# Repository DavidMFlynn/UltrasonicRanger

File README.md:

# UltrasonicRanger
 Puts Ultrasonic range sensors on the serial bus

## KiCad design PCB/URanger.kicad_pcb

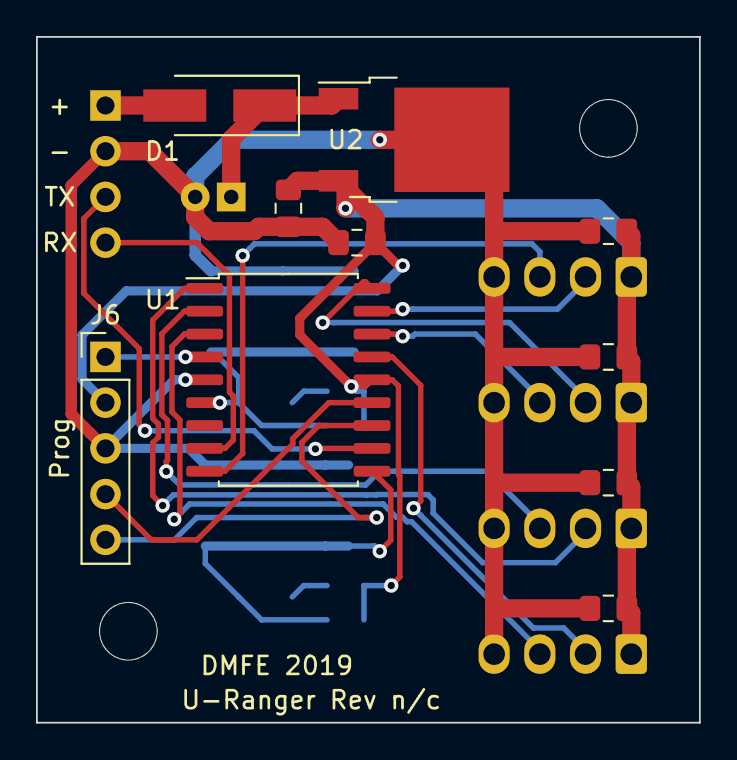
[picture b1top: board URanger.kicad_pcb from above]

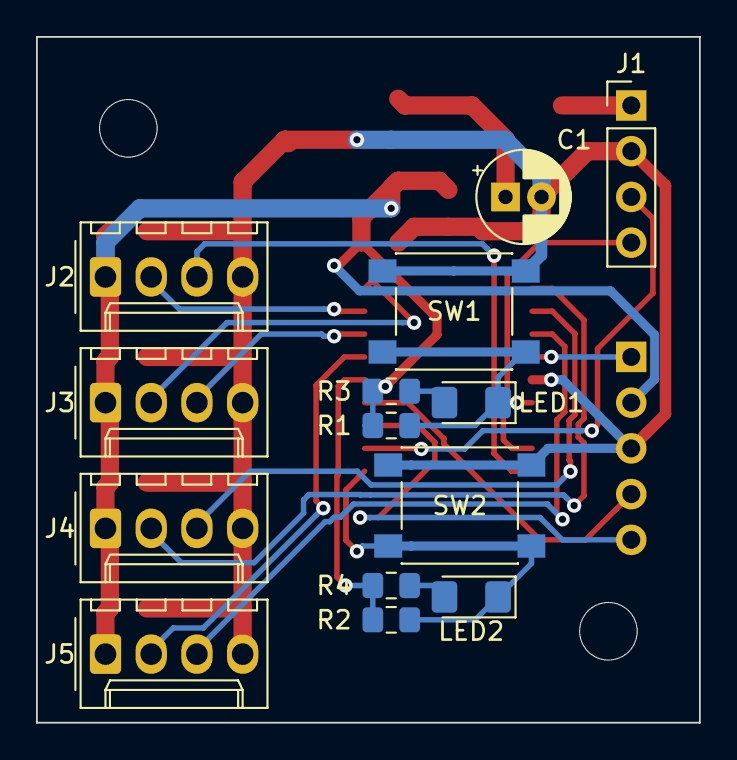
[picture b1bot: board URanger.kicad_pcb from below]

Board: 2 copper layers, 36.8 x 38.1 mm, 26 parts (14 on the bottom side), 21 nets.

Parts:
C1: 2.2uf; CP_Radial_D5.0mm_P2.00mm
C2, C3, C4, C5, C6, C7: 0.1uf; C_0805_2012Metric_Pad1.15x1.40mm_HandSolder
D1: D_ALT; D_SMA_Handsoldering
H1, H2: MountingHole_3.2mm_M3
J1: Conn_01x04; PinHeader_1x04_P2.54mm_Vertical
J2, J3, J4, J5: Conn_01x04; Molex_KK-254_AE-6410-04A_1x04_P2.54mm_Vertical
J6: Conn_01x05; PinHeader_1x05_P2.54mm_Vertical
LED1, LED2: LED_ALT; LED_1206_3216Metric_Pad1.42x1.75mm_HandSolder
R1, R2: 47K; R_0805_2012Metric_Pad1.15x1.40mm_HandSolder
R3, R4: 1.0K; R_0805_2012Metric_Pad1.15x1.40mm_HandSolder
SW1, SW2: SW_Push; SW_SPST_PTS645
U1: PIC16F648A-ISO; SOIC-18W_7.5x11.6mm_P1.27mm
U2: L7805; TO-252-2

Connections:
+5V: C2.1, C3.2, C4.1, C5.1, C6.1, C7.1, J2.1, J3.1, J4.1, J5.1, J6.2, R1.1, R2.1, R3.1, R4.1, U1.14, U2.3
+12V: D1.2, J1.1
Echo1: J2.3, U1.9
Echo2: J3.3, U1.16
Echo3: J4.3, U1.2
Echo4: J5.3, U1.3
GND: C1.2, C2.2, C3.1, C4.2, C5.2, C6.2, C7.2, J1.2, J2.4, J3.4, J4.4, J5.4, J6.3, SW1.1, SW2.1, U1.5, U2.2
ICSPCLK: J6.5, U1.12
ICSPDAT: J6.4, U1.13
unnamed: C1.1, D1.1, U2.1
unnamed: LED1.1, R1.2, SW1.2, U1.6
unnamed: LED1.2, R3.2
unnamed: LED2.1, R2.2, SW2.2, U1.10
unnamed: LED2.2, R4.2
RX: J1.4, U1.8
TX: J1.3, U1.11
Trig1: J2.2, U1.17
Trig2: J3.2, U1.18
Trig3: J4.2, U1.1
Trig4: J5.2, U1.15
Vpp: J6.1, U1.4

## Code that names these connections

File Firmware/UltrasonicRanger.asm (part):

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;   Pin 1 (RA2/AN2) Sensor 3 Trigger Pulse Output
;   Pin 2 (RA3/AN3) CCP3 Sensor 3 Echo Pulse Input
;   Pin 3 (RA4/AN4) CCP4 Sensor 4 Echo Pulse Input
;   Pin 4 (RA5/MCLR*) VPP/MCLR*
;   Pin 5 (GND) Ground
;   Pin 6 (RB0) LED1/SW1 (Active Low Input/Output)(System LED)
;   Pin 7 (RB1/AN11/SDA1) not used
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;
;   Pin 10 (RB4/AN8/SLC1) LED2/SW2 (Active Low Input/Output)
;   Pin 11 (RB5/AN7) TTL Serial TX
;   Pin 12 (RB6/AN5/CCP2) ICSPCLK
;   Pin 13 (RB7/AN6) ICSPDAT
;   Pin 14 (Vcc) +5 volts
;   Pin 15 (RA6) Sensor 4 Trigger Pulse Output
;   Pin 16 (RA7/CCP2) CCP2 Sensor 2 Echo Pulse Input
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; INTOSC oscillator: I/O function on CLKIN pin
; WDT disabled
; PWRT disabled
; MCLR/VPP pin function is digital input
; Program memory code protection is disabled
; Data memory code protection is disabled
; Brown-out Reset enabled
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#Define	Sensor3Trig	LATA,2	;Sensor 3 Trigger Pulse Output
#Define	Sensor3Echo	PORTA,3	;CCP3 Sensor 3 Echo Pulse Input
#Define	Sensor4Echo	PORTA,4	;CCP4 Sensor 4 Echo Pulse Input
#Define	RA5_In	PORTA,5	;VPP/MCLR*
#Define	Sensor4Trig	LATA,6	;Sensor 4 Trigger Pulse Output
#Define	Sensor2Echo	PORTA,7	;CCP2 Sensor 2 Echo Pulse Input
;
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#Define	Sensor1Echo	PORTB,3	;CCP1 Sensor 1 Echo Pulse Input
#Define	SW2_In	PORTB,4	;LED2/SW2 (Active Low Input/Output)
#Define	RB5_In	PORTB,5	;TX Serial Data
#Define	RB6_In	PORTB,6	;ICSPCLK
#Define	RB7_In	PORTB,7	;ICSPDAT
;
SysLED_Bit	EQU	0	;LED1/SW1 (Active Low Input/Output)
LED2_Bit	EQU	4	;LED2/SW2 (Active Low Input/Output)
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
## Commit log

2019-08-04 first comit
2019-08-05 It works!
2019-08-05 PCB ordered
2019-08-06 Auto Trigger
2019-08-30 Added dwell
2019-09-02 Added Lidar-Lite option to J5
